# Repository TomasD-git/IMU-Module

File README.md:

# IMU-Module  
Simple IMU module, uses LSM6DSOXTR as IMU and XC6228D332VR-G as LDO    
I made this because most IMU have some sort of fallback, either bad imu, no ldo on board etc.. 

<details>
  <summary>BOM</summary>
  
| Name|Purpose|Quantity|Total Cost (USD)|Link|Distributor |  
| ----|-------|--------|----------------|----|----------- |
| PCB + stencil|all components are on this|5|8|https://jlcpcb.com|jlcpcb |  
| ALL components|all components that are on pcb|1|10|https://lcsc.com|lcsc|  
|  |  |  Total cost|38| | |  

</details>

In production folder, is lcsc bom which has all components ready to import to lcsc, and gerber files and placement if using pcba.  

# Pictures  

**Schematic**  
  
**PCB**  
  
**3D Viewer**

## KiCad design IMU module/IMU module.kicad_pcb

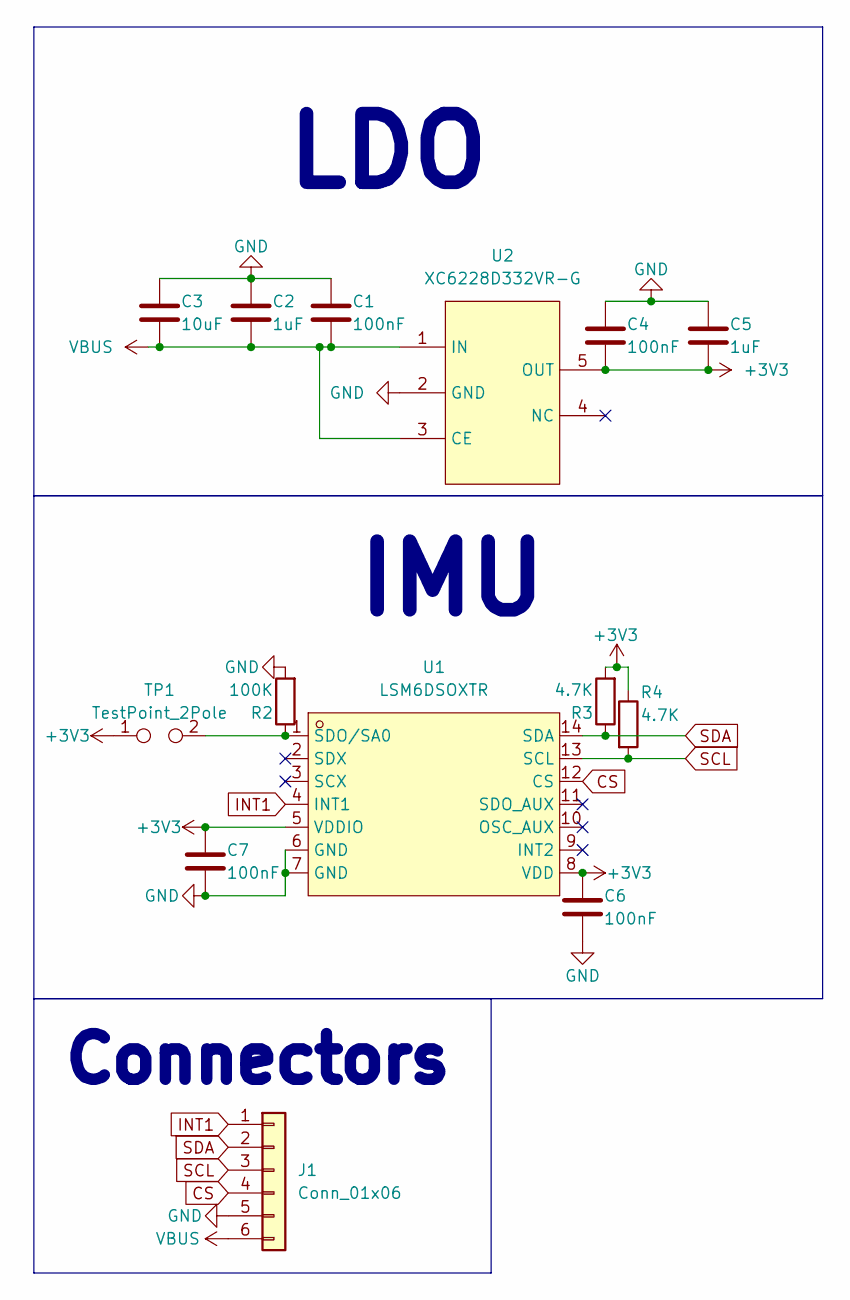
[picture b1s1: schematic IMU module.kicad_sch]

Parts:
C1, C4, C6, C7: 100nF; C_0402_1005Metric
C2, C5: 1uF; C_0603_1608Metric
C3: 10uF; C_0805_2012Metric
J1: Conn_01x06; PinHeader_1x06_P2.54mm_Vertical
R2: 100K; R_0603_1608Metric
R3, R4: 4.7K; R_0402_1005Metric
TP1: TestPoint_2Pole; SolderJumper-2_P1.3mm_Open_TrianglePad1.0x1.5mm
U1: LSM6DSOXTR; LGA-14L_L3.0-W2.5-P0.50-TL; MPN LSM6DSOXTR; LCSC Part C481766
U2: XC6228D332VR-G; SOT-25-5_L3.0-W1.8-P0.95-LS3.0-BR; MPN XC6228D332VR-G; LCSC Part C69841

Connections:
+3V3: C4.2, C5.2, C6.1, C7.1, R3.2, R4.1, TP1.1, U1.5 (VDDIO), U1.8 (VDD), U2.5 (OUT)
CS: J1.4, U1.12 (CS)
GND: C1.1, C2.1, C3.1, C4.1, C5.1, C6.2, C7.2, J1.5, R2.2, U1.6 (GND), U1.7 (GND), U2.2 (GND)
INT1: J1.1, U1.4 (INT1)
unnamed: R2.1, TP1.2, U1.1 (SDO/SA0)
SCL: J1.3, R4.2, U1.13 (SCL)
SDA: J1.2, R3.1, U1.14 (SDA)
VBUS: C1.2, C2.2, C3.2, J1.6, U2.1 (IN), U2.3 (CE)

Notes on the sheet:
LDO
Connectors
IMU

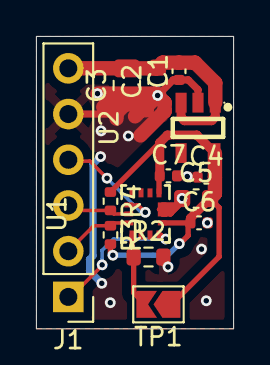
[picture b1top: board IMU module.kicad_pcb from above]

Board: 2 copper layers, 11.0 x 16.2 mm, 14 parts (0 on the bottom side), 8 nets.

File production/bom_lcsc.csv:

Designator,Footprint,Quantity,Value,LCSC Part #
"C1, C4, C6, C7",0402,4,100nF,C152814
"C2, C5",0603,2,1uF,C519560
C3,0805,1,10uF,C5137471
J1,PinHeader_1x06_P2.54mm_Vertical,1,Conn_01x06,
R2,0603,1,100K,C2907088
"R3, R4",0402,2,4.7K,C48392572
TP1,SolderJumper-2_P1.3mm_Open_TrianglePad1.0x1.5mm,1,TestPoint_2Pole,
U1,LGA-14L_L3.0-W2.5-P0.50-TL,1,LSM6DSOXTR,C481766
U2,SOT-25-5_L3.0-W1.8-P0.95-LS3.0-BR,1,XC6228D332VR-G,C69841

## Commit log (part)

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2026-06-23 added files
